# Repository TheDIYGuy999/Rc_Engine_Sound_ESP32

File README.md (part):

# This is an Arduino RC engine sound & light controller for ESP32

It's based on the ATmega 328 version: https://github.com/TheDIYGuy999/Rc_Engine_Sound
and on bitlunis Halloween example: https://github.com/bitluni/MotionPumpkin

Wiring and software installation instructions see further down.
Arduino IDE or Visual Studio Code (with Platform IO extension) are supported.

Video series: https://www.youtube.com/playlist?list=PLGO5EJJClJBCjIvu8frS7LrEU3H2Yz_so

************************************************************************
You can find the changes in the [Changelog](documentation/Changelog.md).
************************************************************************

Discussion and support thread (in German & English): https://www.rc-modellbau-portal.de/index.php?threads/esp32-arduino-rc-sound-und-licht-controller.7183/

Fully assembled, tested and working 30 pin SMD version with switch mode PSU & display connector.
Order it here: https://www.pcbway.com/project/shareproject/Arduino_RC_engine_sound_light_controller_for_ESP32_a9334731.html

New: STL data for nice 3D printed housing available:
https://thediyguy999.github.io/TheDIYGuy999_ESP32_Web_Flasher/products.html

New: Compact version for trailer or tractor:
https://thediyguy999.github.io/TheDIYGuy999_ESP32_Web_Flasher/products.html

New: RZ7886 7A ESC:
https://thediyguy999.github.io/TheDIYGuy999_ESP32_Web_Flasher/products.html

New: wireless built-in configuration website 192.168.4.1

New: LCD dashboard (original by Frevic)

https://www.facebook.com/profile.php?id=100066616574355

LCD dashboard (original by Gamadril)

Fully assembled, tested and working 30 pin SMD version, manufactured and pre-assembled by https://www.pcbway.com

Fully assembled, tested and working 30 pin thru hole version

Compact version for excavator (IBUS & sound only, supplied by 6V BEC)

## Features:
- Unique vehicle mass inertia simulation (connect your crawler type ESC to pin 33). Throttle output is altered during shifting of a mechanical 3 speed transmission for smooth shifting, gear protection and realistic sound. Works just fine with TAMIYA 3 speed transmissions. Should work as well with crawler 2 speed transmissions. The ESC is controlled by a state machine with the following states: driving forward & reverse (varible acceleration, depending on throttle position), neutral, braking forward & reverse (variable deceleration with fine granularity, according to "reverse throttle" position). It also allows to control the brake lights, the brake sound, the reversing light & the reversing beep sound properly. Acceleration & deceleration (coasting & braking) are adjustable separately for each gear to ensure maximum realism.
- Unique "virtual clutch" allows to rev the engine below an adjustable ESC output speed. Above, the clutch engages and ensures, that the engine sound is in synch with the wheel RPM. Sounds and behaves just great in combination with a shifting transmission!
- Simulated automatic transmission with torque converter (if your vehicle does not have a real shifting transmission)
- Simulated double clutch transmission
- simulated, manually shifted 3 speed transmission (new in v5.5)
- Virtual, switchable neutral allows to rev the engine while standing still
- Jake brake (simulated pneumatic engine brake, mainly used in US trucks)
- Tracked mode (dual throttle input on CH2 & CH3, for tanks, diggers etc. No ESC control support in this mode. (New in v4.5)
- Tank cannon sound & flash (New in v4.6)
- Triggering multiple latching and non latching actions (sounds, lights) per analog channel, using the rcTrigger library (New in v4.7, still experimental)
- Many selectable sounds: engine cranking, engine idling, engine revving, turbo whining, diesel ignition "knock", wastegate valve, horns, sirens, reversing beep, air brake, parking brake, gear shifting etc.
- Realistic engine sound is mixed together on the fly from up to 4 sounds: engine idling, turbo, wastegate (all with variable sampling rate), Diesel ignition knock (fixed sampling rate, so it does not vary in pitch)
- Load (throttle position) dependent volume sounds: idle, rev, Diesel knock
- Engine RPM dependent volume sounds: turbo, wastegate
- Dozens of engine & other sounds included, you can also compose your own, using Audacity and bitlunis conversion tool (link above)
- Engine RPM range and inertia adjustable, volume of all sounds adjustable, engine sounds separatly for load and idling.
- Many other paramerets can be adjusted. All adjustments are easily accessible in "adjustmentsXyz.h"
- Sound files up to 22'050Hz, 8bit, mono can be used
- Compatible input signals: PWM, PPM, SBUS (inverted & non inverted signals), IBUS
- Works best with a PAM8403 amplifier module, connected to pin 25 & 26, via 10kOhm resistors & a 10kOhm potentiometer (see schematic below)
- The engine RPM is calculated according to RC signal input on pin 13 *** CAUTION, 3.3V max. on all pins! *** 330 Ohm resistors on all I/O pins recommended!
- Non linear throttle curves can be generated in "curves.h"
- Light effects: headlights (high & low beam), tail lights, brake lights, fog lights, roof lights, cab lights, reversing light, indicators (turn signals), hazard lights, blue light etc. (max. 12 outputs)
- Engine vibration simulation, using a shaker motor with excentric weight: Strong vibration while cranking, medium wlile idling, slight while revving
- Adjustable volume (via remote)
- Use an ESP32, CPU frequency must be set to 240MHz
- Eagle schematic & board file included. Pre made Gerber files allow you to order your board easily.
- included, easy to use .wav to .h sound file converter
- Channels can easily be assigned, using "remoteSetup.h"
- Pre made configuration profiles for Flysky FS-i6X and Arduino Mirco RC remote (new in v.5.5)
- Variable length for horn & siren, using loop area in sound files (new in v5.6)
- BUS decoder for steering servo and shifting servo (connect servos to CH1 & CH2) pins
- Trailer coupler (5th wheel) servo can be connected to the CH4 pins (not in PWM communication mode)
- TAMIYA trailer presence switch can be connected to pin 32 (depending on "#define THIRD_BRAKELIGHT" setting in "6_adjustmentsLights.h" tab)
- Support for non linear throttle and steering curves (for more accurate control around center position). Use "EXPONENTIAL_THROTTLE" & "EXPONENTIAL_STEERING" in "2_adjustmentsRemote.h"
- Support for HOBBYWING Quicrun Fusion Motor / ESC combo. Use "#define QUICRUN_FUSION" in "3_adjustmentsESC.h"
- Support for winch, connected to CH3 (BUS communication mode only). Use "#define MODE2_WINCH" in "7_adjustmentsServo.h" The mode 2 button is then used to switch between horn / siren sontrol and winch control via CH4. The winch is controlled by an old RC servo driver board. The speed and neutral settings are done using "CH3L", CH3C" and CH3R" positions.
- Support for LCD dashboard
- Support for 2812 Neopixel LED (GPIO0)
- Support for hydlaulic excavators (hydraulic pump, hydraulic flow, track rattling sounds). Use #define FLYSKY_FS_I6S_EXCAVATOR profile for remote
- ESP-NOW based 2.4 GHz wireless trailer control support
- An RZ7886 motor driver IC can be used instead of a standard crawler type RC ESC
- Battery low discharge protection options
- Switchable crawler mode (with just minimal virtual inertia)
- Wireless configuration website 192.168.4.1

## On the todo list:
- cornering lights (on the beacon outputs)
- Hazards switching on, if engine off in AUTO_LIGHTS mode

## Known issues:
- Arduino IDE 1.8.7 or older is not supported and will cause compiler errors!
- The ESP32 does not work on macOS Big Sur 11.x, but this issue can be fixed easily as described here: [Big Sur Fix](BigSurFix.md) (for v1.04)
- macOS Monterey 10.3 does not include Python 2 anymore. For Arduino IDE, you have to install Python 3 and to change the path in pPlatform.txt according to:
https://forum.arduino.cc/t/mac-os-update-killed-esp32-sketch/969580/24

## How to create new .h sound files:

### Audacity:
- import the WAV sound file you want in Audacity
- convert it to mono, if needed
- on the bottom left, select project frequency 22'050Hz
- search for a cyclic pattern in the idle sound (the amount of ignition pulses is usually the same as the cylinder number), cut the "idle" sample to exactly this length, have a close look at the zero crossings to avoid clicking noises. The loudest peak should always be at the end of the sample.
- do the same with the "rev" sound. It will be 2 - 4 times shorter than the "idle" sample, depending on the engine and rpm of the "rev" sample
- change the "Rate" (dropdown on the left of the sample) of the "rev" sample, until the length is the same as in the "idle" sample. This is very important!
- duplicate a part of the "rev" sample (the one with the original, unchanged "Rate" speed). This is the "knock" sample. Cut it to this max length: "Idle" length / number of cylinders / rpm range "MAX_RPM_PERCENTAGE" (usually 2 - 4 or 200 - 400%)
- adjust the volume of all samples, so that the entire dynamic range is used
- you may also want to apply high pass or low pass filters to fine tune the sound
- select > export audio > selected audio > WAV > 8-bit-PCM

### Convert the .wav file with the modified converting tool (new in v5.2):

- open the included "Audio2Header.html" converter in your browser. It is located in the "tools" folder
- adjust the export file format (no changes required)
- select the export file type, depending on the sound you are converting (idle, rev, horn etc.)
- open the wav file you want to convert
- a .h file is generated and downloaded
- move it to your "sketch/vehicles/sounds" directory

### Include the new header file with your sound in your vehicle preset, adjust settings until you are happy:
- include this .h file in "Adjustments.h" > "yourVehiclePreset.h"
- knock sound settings:
  - "dieselKnockInterval" = number of cylinders
  - uncomment "V8" for V8 engines, R6 for inline 6 engines or "V2" for V2 (Harley) engines
  - adjust "dieselKnockAdaptiveVolumePercentage" (how loud the "silent" knock pulses are compared with the loud ones), only active, if defined "V8", "R6"  or "V2"
- play with the other volumes, start-, end- and switch-points until you are happy
- the "rev" sound is optional and only active, if "REV_SOUND" is defined (// removed)
- adjust the transition from the "idle" to the "rev" sound, using "revSwitchPoint", "idleEndPoint", "idleVolumeProportionPercentage". This step is very important and can make a huge difference!

### Compile the new sketch:
- compile and upload the sketch in Arduino IDE
- the new sound should now be ready

## Schematic example (use PDF for current version!):

## PCB
### Included PCB files:
- See hardware folder

### Recommended manufacturer:
https://www.pcbway.com (including SMD assembling service, use Gerbers.zip for board, it also includes BOM. xlsx and CPL.xlsx, if you want to use the SMT assembling service)
How to order pre assembled boards see /Eagle_PCB/How To Order Your PCB.pdf

### The easiest way to order the 30pin SMD version with display connector:
https://www.pcbway.com/project/shareproject/Arduino_RC_engine_sound_light_controller_for_ESP32_a9334731.html

### Assembling tutorial (for the 30 pin SMD version without display connector):
https://www.youtube.com/watch?v=csQgTfxRd8Y&t=2s

### Assembling tutorial (for the 36 pin version):
https://www.youtube.com/watch?v=Vfaz3CzecG4&list=PLGO5EJJClJBCjIvu8frS7LrEU3H2Yz_so&index=13

## Wiring:
### Before you begin:
- This device is not protected against wrong polarity!
- Always use series resistors for LED headers (except TAMIYA trailer header)
- Maximum input voltage on "Sig" pins = 3.3V (be careful with very old receivers, which may deliver 5V)
- It is recommended to use a fuse between your battery and the sound controller / ESC

### Supply for audio amplifier, shaker motor and LED:
- Use an Y-cable between your battery, your ESC and The "X1" terminal. Battery voltage range is 7 - 12.6V

### Supply for ESP32:
- The ESP32 is not supplied through the "X1" terminal
- It can be supplied through the Micro USB header
- or through the +V and GND pin row on the top of the board (the voltage is usually coming from the BEC in your ESC, which needs to be connected to the "ESC" header)

### ESC wiring:
- Connect a Hobbywing 1080 ESC to the ESC header (GND, V+ and Sig)
- Adjust the ESC parameters, using the programming card as described on the top of "Adjustments.h"
- I do not recommend any other ESC
- The ESC is controlled by the cound controller, rather than directly by the receiver. This allows to use the unique "virtual inertia" feature. NOTE: Use this feature at your own risk! I'm not responsible, if any damage is caused. It's running very stable and I never had an issue, but you never know.
- "escPulseSpan" can be used to limit the top speed of your vehicle. 500 = not limited, anything above 500 will limit the top speed

### Receiver wiring for PWM servo signals (the most common wiring):
- Channel assignment according to "remoteSetup.h" and remoteSetup.xlsx", easily adjustable (new in v5.5). It is important to plug in the wires according to the channel assignment
- CH5 & 6 are coming in via the "35" & PPM" headers
- At least one CH needs to be connected, using a 3 pin wire, so that GND and V+ are connected as well (receiver supply)
- CH1 - 4 headers are pairs, wired in parallel. This allows to feed servo signals through, eliminating the need for Y-cables
- Note that you need to change the configuration as described below, if you want to use this wiring method

### Receiver wiring for PPM signals:
- Internal channel assignment as above
- Connect a 3 pin wire fom your receiver PPM header to the RX (changed in v5.5, was PPM) header on the sound controller (Sig, V+, GND)
- Note that you need to change the configuration as described below, if you want to use this wiring method
- 8 channels can be read in this mode

### Receiver wiring for SBUS signals (recommended):
- Internal channel assignment as above
- Connect a 3 pin wire fom your receiver SBUS header to the SBUS header on the sound controller (Sig, V+, GND)
- The "Sig" pin on the SBUS header is 5V tolerant
- 13 channels can be read in this mode

### Receiver wiring for IBUS signals:
- Internal channel assignment as above
- Connect a 3 pin wire fom your receiver IBUS header to the RX header on the sound controller (Sig, V+, GND)
- 13 channels can be read in this mode

### Speakers
- 4 or 8 ohms speakers are compatible
- You can use one or two speakers
- never use two speakers in parallel on a single header
- never use two headers in parallel to drive one speaker
- never connect capacitors to the speaker headers

### LED
- The LED need to be wired "common positive". This means, the long LED legs are all connected together and connect to the 5V rail, coming from the on board regulator
- All LED (except the ones, which are connected to the TAMIYA trailer connector) need a series resistor
- Calculate the reqired resistor according to: http://ledcalc.com (supply voltage = 5V)
- It is not recommended to wire LED in parallel, sharing the series resistor
- Support for WS2812 Neopixel LED (details and wiring see "6_adjustmentsLights.h")

### LCD dashboard
- See "9_adjustmentsDashboard.h"

### Shaker
- The shaker is used for engine vibration simulation. The speed can be adjusted in the vehicle configuration and will vary depending on the engine state and rpm
- It needs to be connected to the "shaker" header and is supplied by the on board 5V regulator. The negative side is switched by the on board mosfet
- Please note, that the used mosfet needs to be a logic level type. Otherwise the shaker will not work!
- The motor should not draw more than about 300mA @ 5V. I'm using a shaker motor from GT Power.

### RZ7886 7A DC motor driver instead of an ESC:
It is intended for smaller scale vehicles like WPL

#### Prototype:

#### Order your motor driver PCB here:
https://www.pcbway.com/project/shareproject/RZ7886_based_ESC_for_ESP32_Sound_and_Light_Controller_f8f4a805.html

## Software:
### Required software for code uploading and editing:
- Arduino IDE (not recommnded): https://www.arduino.cc/en/Main/Software
- or Visual Studio Code with PlatformIO extension (recommended): https://code.visualstudio.com
- Visual Studio also requires this software (restart VS Code afterwards) in order to be able to synchronise libraries: https://git-scm.com/download

### Downloading and preparing the code with Arduino IDE:
- Download the code from here (hit "Code > Download zip"): https://github.com/TheDIYGuy999/Rc_Engine_Sound_ESP32
- Unzip the folder, if required
- Remove the "-master" part of the folder name
- Install libraries and board definitions below first, restart Arduino IDE
- Open "scr.ino" with a double click (Arduino IDE should start)

### Required ESP32 board definition (not required, if Visual Studio Code is used as IDE):
- Install it according to: https://randomnerdtutorials.com/installing-the-esp32-board-in-arduino-ide-windows-instructions/
- Use v1.04, v1.05 or newer are causing reboot issues!
- Adjust settings according to:

### Required libraries. You need to install ALL of them, if using Arduino IDE. Not required, if Visual Studio Code is used as IDE:
- statusLED: https://github.com/TheDIYGuy999/statusLED
- SBUS: https://github.com/TheDIYGuy999/SBUS
- rcTrigger: https://github.com/TheDIYGuy999/rcTrigger
- IBUS: https://github.com/bmellink/IBusBM
- TFT: https://github.com/Bodmer/TFT_eSPI
- FastLED: https://github.com/FastLED/FastLED    

Download them in the same manner as the main code above. Store the folders in your "Arduino/libraries" path.
Install them according to: https://www.arduino.cc/en/Guide/Libraries

### Uploading the code to the board:
- IMPORTANT: Depending on your board, you may have to press and hold the "BOOT" button, if the IDE just shows "Connecting........_____...." Release it, as soon as the upload starts.
- On macOS Big Sur, you need to apply the following fix (Arduino IDE only):  [Big Sur Fix](BigSurFix.md)

### Visual Studio Code (instead of Arduino IDE) overiew:

## Adjusting things in "X_Xyz.h":
### Vehicle selection:

Note, that in v5.5 the former "Adjustments.h" configuration file was divided into multiple files.

Uncomment (remove //) the vehicle you want in "Adjustments.h". Never uncomment more than one vehicle!
Note, that you need to re-upload the code after you changed the settings. Otherwise it will not take effect.
Select >Sketch > Upload to upload the code. Important! Always lift your vehicle off the ground while uploading.

If you want to make a new vehicle, copy vehicles/00_Master.h, store it with your vehicle name. Then edit the settings as you like, add links to the sound files you want.
Afterwards add a link to your vehicle.h (see examples below) and uncomment it

```
#include <Arduino.h>

// VEHICLE SETTINGS ****************************************************************************************************
// Select the vehicle preset you want (uncomment the one you want, remove //, never more than one)

// Master --------
//#include "vehicles/00_Master.h" // This master preset file contains all available sound files, which are not used in existing vehicle presets

// US trucks --------
//#include "vehicles/CaboverCAT3408.h" // Cabover truck with Caterpillar 3408 V8 Diesel
//#include "vehicles/PeterbiltDetroit8v92.h" // Peterbilt 359 with Detroit 8V92 V8 2 stroke Diesel
//#include "vehicles/KenworthW900ADetroit8V71.h" // Kenworth W900A with Detroit 8V71 V8 2 stroke Diesel
//#include "vehicles/KenworthW900ACAT3408.h" // Kenworth W900A with Caterpillar 3408 V8 Diesel (King Hauler)
//#include "vehicles/CAT3408OpenPipes.h" // Kenworth W900A with Caterpillar 3408 V8 Diesel and open pipes
//#include "vehicles/KenworthW900ACAT3408new.h" // Kenworth W900A with Caterpillar 3408 V8 Diesel (good bass speaker required)
//#include "vehicles/KenworthCummins335.h" // 1950ies Kenworth with Cummins 335 R6 Diesel
//#include "vehicles/MackSuperLiner.h" // MACK Super Liner
//#include "vehicles/M35.h"// AM General M35 "deuce and a half" military truck, turbocharged R6 universal fuel engine
//#include "vehicles/US_Firetruck.h"// US firetruck with CAT3408 V8 and Allison 6 speed automatic (horn & siren loop capable)
//#include "vehicles/FreightlinerCummins350.h" // Freightliner Cabover with Cummins 350 R6 Diesel

// EU trucks --------
//#include "vehicles/Tatra813.h" // Tatra 813 8x8 V12 Diesel military truck (old version for comparison, don't use it)
//#include "vehicles/Tatra813new.h" // Tatra 813 8x8 V12 Diesel military truck
//#include "vehicles/UnimogU1000.h" // Umimog U 1000 with turbocharged R6 Diesel incl. Feuerwehr "Martinshorn" siren
//#include "vehicles/MercedesActros1836.h" // Mercedes Actros 1863 or 3363 truck with R6 Diesel
//#include "vehicles/MercedesActrosV6.h" // Mercedes Actros V6 Race Truck incl. tire squealing
//#include "vehicles/ScaniaV8_50ton.h" // SCANIA V8 50 ton truck. Unknown model. Bad quality!
//#include "vehicles/ScaniaV8.h" // SCANIA V8 truck, unknown model
//#include "vehicles/1000HpScaniaV8.h" // 1000 HP SCANIA V8 truck with open pipes. Insane sound! Good bass speakers reqired
//#include "vehicles/Scania143.h" // SCANIA 143 V8 - the legend! The best sounding in my opinion
//#include "vehicles/ScaniaV8Firetruck.h" // SCANIA V8 firetruck, automatic Allison 6 speed transmission with torque converter, "Martinshorn" siren
//#include "vehicles/VolvoFH16_750.h" // Volvo FH16 750 truck. Inline 6, 750 horses, open pipes!
//#include "vehicles/VolvoFH16_OpenPipe.h" // Volvo FH truck. Inline 6, open pipes, alternative version
//#include "vehicles/ManTgx.h" // MAN TGX 680 V8 truck
//#include "vehicles/ManKat.h" // MAN KAT V8 Diesel German Bundeswehr military truck
//#include "vehicles/MagirusDeutz256.h" // Magirus Deutz 256 air coolded V8 Diesel truck
//#include "vehicles/MagirusMercur125.h" // Magirus Mercur air coolded V6 Diesel truck
//#include "vehicles/Saurer2DM.h" // Swiss Saurer 2DM R6 Diesel truck

// Russian trucks --------
//#include "vehicles/Ural4320.h" // URAL 4320 6x6 V8 Diesel military truck
#include "vehicles/Ural375D.h" // URAL 375D 6x6 V8 petrol military truck
//#include "vehicles/URAL375.h" // URAL 375D 6x6 V8 petrol military truck (new version with better V8 sound, but good bass speaker required)
//#include "vehicles/GAZ66.h" // GAZ-66 V8 petrol military truck

// Russian tanks -------
//#include "vehicles/IS3.h" // IS-3 WW2 battle tank, V12 Diesel (dual ESC mode, good bass speaker required)

// Tractors -------
//#include "vehicles/KirovetsK700.h" // Russian Kirovets K700 monster tractor. Extreme turbo sound!

// Excavators -------
//#include "vehicles/Caterpillar323Excavator.h" // Caterpillar 323 excavator (use "FLYSKY_FS_I6S_EXCAVATOR" remote profile)

// Dumpers -------
//#include "vehicles/Benford3TonDumper.h" // Benford 3 ton dumper

// US motorcycles --------
//#include "vehicles/HarleyDavidsonFXSB.h" // Harley Davidson FXSB V2 motorcycle

// US cars --------
//#include "vehicles/ChevyNovaCoupeV8.h" // 1975 Chevy Nova Coupe V8
//#include "vehicles/1965FordMustangV8.h"// 1965 Ford Mustang V8
//#include "vehicles/Chevy468.h" // Chevy 468 big block V8

// EU cars --------
//#include "vehicles/VwBeetle.h" // VW Käfer / Beetle
//#include "vehicles/JaguarXJS.h" // Jaguar XJS V12, manual transmission
//#include "vehicles/JaguarXJSautomatic.h" // Jaguar XJS V12, automatic transmission
//#include "vehicles/MGBGtV8.h" // MGB GT V8, manual transmission
//#include "vehicles/LaFerrari.h" // Ferrari LaFerrari, V12, 6 speed double clutch transmission

// US SUV & Pickups --------
//#include "vehicles/JeepGrandCherokeeTrackhawk.h" // Jeep Grand Cherokee Trackhawk V8 monster SUV with supercharger, 6 speed automatic
//#include "vehicles/FordPowerstroke.h" // Ford Powerstroke 7.3l V8 Diesel, 6 speed automatic (good bass speaker required)
//#include "vehicles/RAM2500_Cummins12V.h" // Dodge RAM 2500 with inline 6, 12V Cummins 5.9l Diesel, manual transmission
//#include "vehicles/RAM2500_Cummins12Vautomatic.h" // Dodge RAM 2500 with inline 6, 12V Cummins 5.9l Diesel, automatic transmission
//#include "vehicles/GMCsierra.h" // GMC Sierra V8 pickup, 3 speed automatic transmission
//#include "vehicles/ChevyNovaCoupeV8_P407.h" // 1975 Chevy Nova Coupe V8, special version for HG-P407, 3 speed automatic transmission
//#include "vehicles/JeepWranglerRubicon392V8.h" // 2021 Jeep Wrangler Rubicon HEMI 392 V8 (starter needs rework)
//#include "vehicles/JeepWranglerRubicon392V8_2.h" // 2021 Jeep Wrangler Rubicon HEMI 392 V8 (insane bass!)

// EU SUV --------
//#include "vehicles/DefenderV8Automatic.h" // Land Rover Defender 90 V8 automatic (very nice V8 with lots of bass)
//#include "vehicles/DefenderV8OpenPipeAutomatic.h" // Land Rover Defender 90 V8 automatic, open pipes (optimised for smaller speakers)
//#include "vehicles/DefenderV8CrawlerAutomatic.h" // Land Rover Defender 90 V8 automatic crawler
//#include "vehicles/DefenderTd5.h" // Land Rover Defender 90 Td5 R5 Diesel

// Asian SUV --------
//#include "vehicles/LandcruiserFJ40.h" // Landcruiser Fj40 with inline 6 petrol engine
//#include "vehicles/LandcruiserFJ40Diesel.h" // Landcruiser Fj40 with inline 6 12H Turbo Diesel engine
//#include "vehicles/LandcruiserFJ40Diesel2.h" // Landcruiser Fj40 with inline 6 12H Turbo Diesel engine
//#include "vehicles/HiluxDiesel.h" // Hilux Diesel with inline 6 12H Turbo Diesel engine (for HG-P407)

// US locomotives --------
//#include "vehicles/UnionPacific2002.h" // Union Pacific 2002 SD70M locomotive with enormous, low revving 16 cylinder Diesel

// Planes --------
//#include "vehicles/MesserschmittBf109.h" // Messerschmitt BF 109 WW2 German V12 plane

// Generic Diesels --------
//#include "vehicles/generic6zylDiesel.h" // Generic inline 6 Diesel, no turbo, manual transmission (optimised for smaller speakers)
```

### Interface type (communication mode) selection:

Note, that the default communication mode is SBUS. You need to change it as follows, if you want to use classic RC servo signals.

#### PWM (classic RC signals on "CH1" - "CH4", "35" & "PPM" headers, the most common interface)
```
// COMMUNICATION SETTINGS **********************************************************************************************
// Choose the receiver communication mode (never uncomment more than one!) !!! ADJUST THEM BEFORE CONNECTING YOUR RECEIVER AND ESC !!!

// PWM servo signal communication (CH1 - CH4, 35, PPM headers, 6 channelschannelSetup.h) --------
// PWM mode active, if SBUS, IBUS and PPM are disabled (// in front of #define)

// SBUS communication (SBUS header, 13 channels. This my preferred communication protocol)--------
//#define SBUS_COMMUNICATION // control signals are coming in via the SBUS interface (comment it out for classic PWM RC signals)
boolean sbusInverted = true; // false = wired to non standard (inverted) SBUS signal (for example from "Micro RC" receiver)

// IBUS communication (RX header, 13 channels not recommended, NO FAILSAFE, if bad contact in iBUS wiring!) --------
//#define IBUS_COMMUNICATION // control signals are coming in via the IBUS interface (comment it out for classic PWM RC signals)

// SUMD communication (RX header, 12 channels, For Graupner remotes) --------
//#define SUMD_COMMUNICATION // control signals are coming in via the SUMD interface (comment it out for classic PWM RC signals)

// PPM communication (RX header, 8 channels, working fine, but channel signals are a bit jittery) --------
//#define PPM_COMMUNICATION // control signals are coming in via the PPM interface (comment it out for classic PWM RC signals)
```

#### PPM (multiple channels pulse pause modulation, wired to "RX" header, 8 channels)
```
// COMMUNICATION SETTINGS **********************************************************************************************
// Choose the receiver communication mode (never uncomment more than one!) !!! ADJUST THEM BEFORE CONNECTING YOUR RECEIVER AND ESC !!!

// PWM servo signal communication (CH1 - CH4, 35, PPM headers, 6 channelschannelSetup.h) --------
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
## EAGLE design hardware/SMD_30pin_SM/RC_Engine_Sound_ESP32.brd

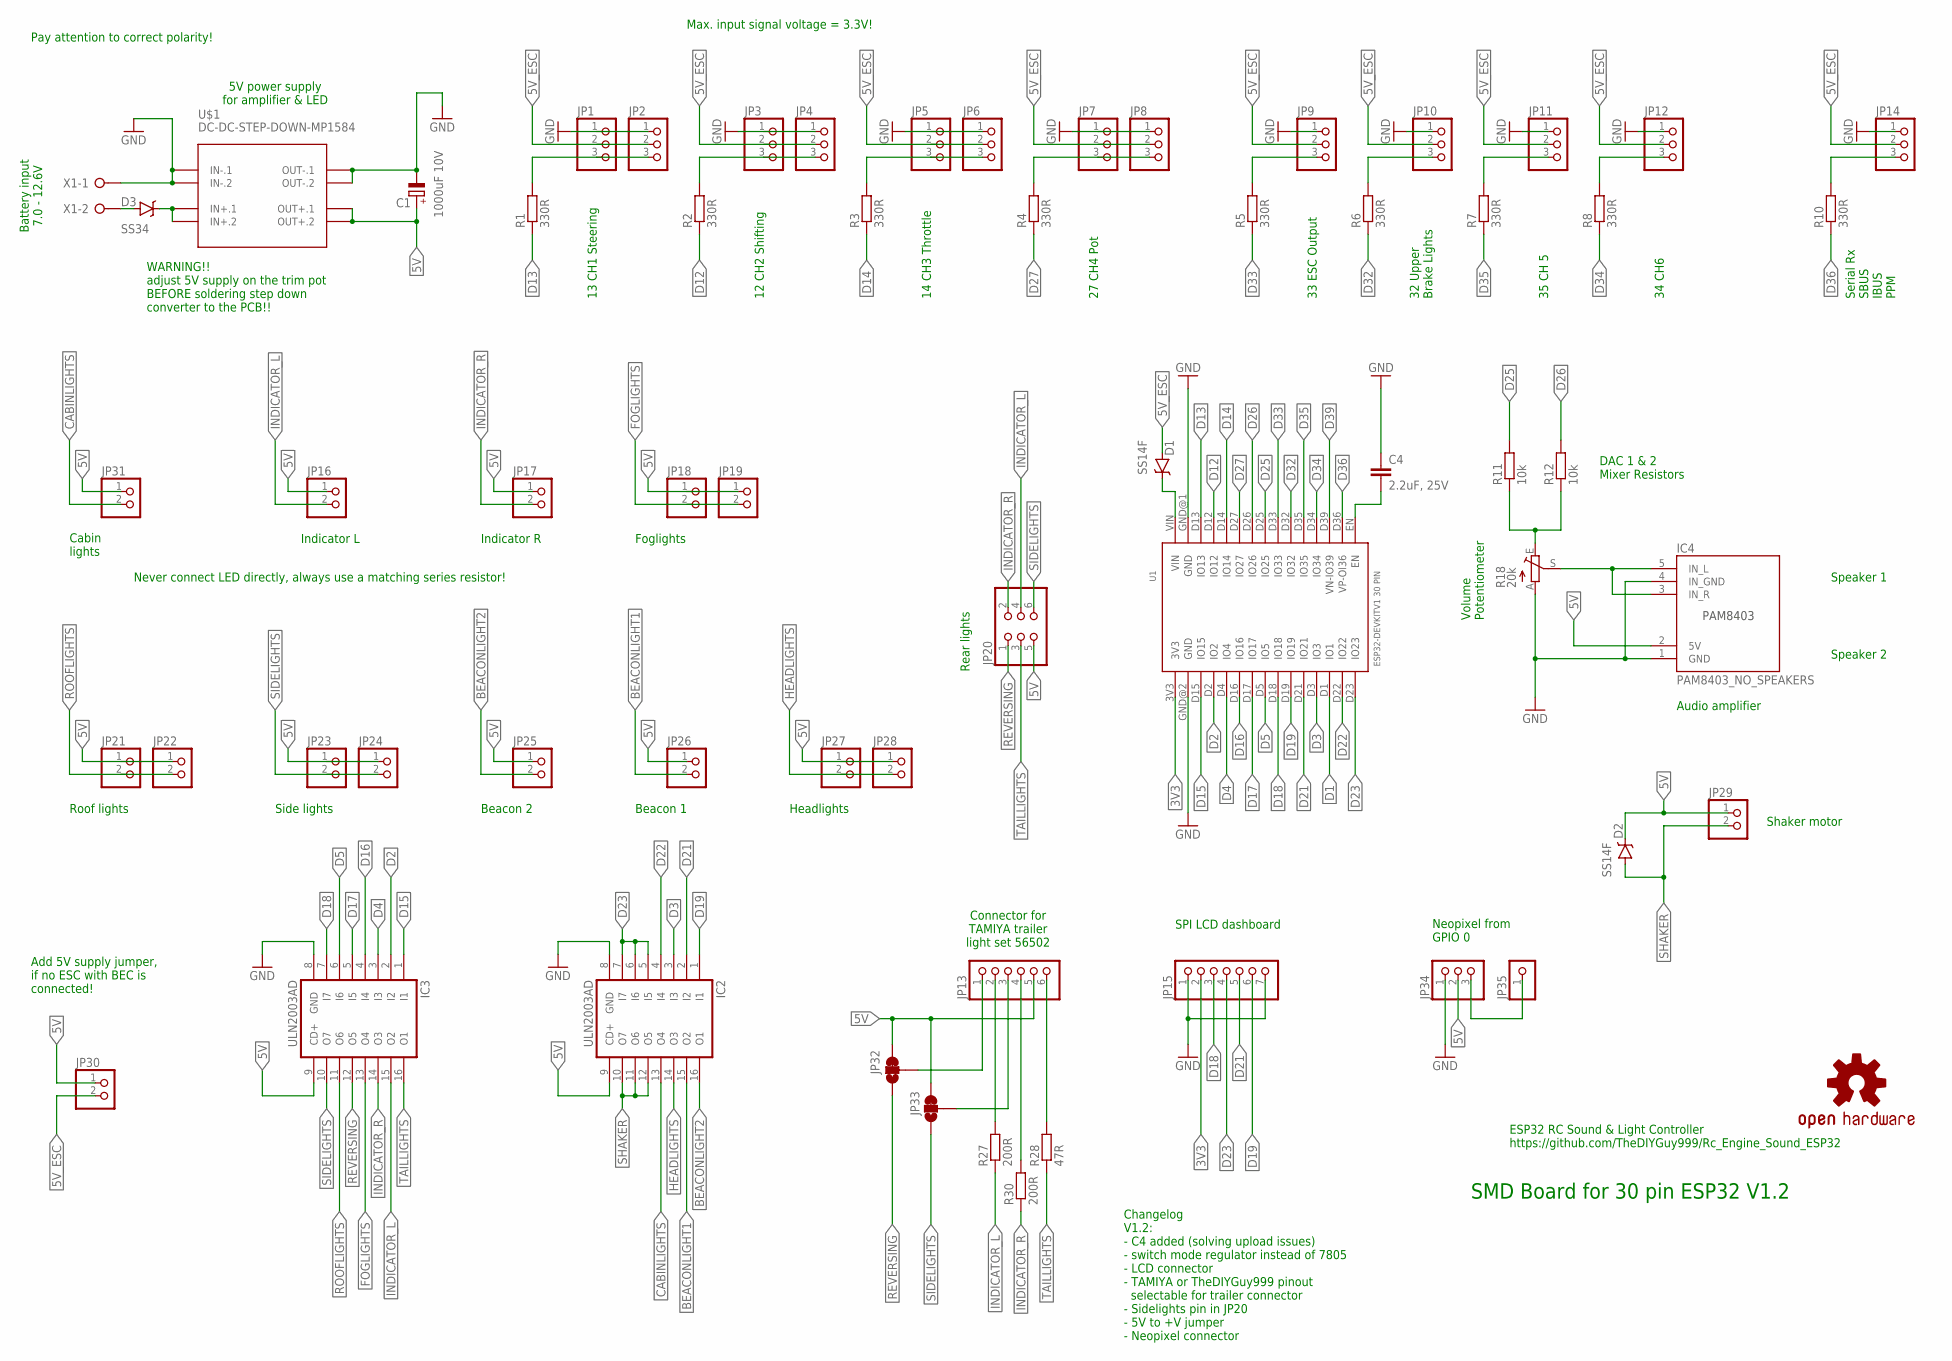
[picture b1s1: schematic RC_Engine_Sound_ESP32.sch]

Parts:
C1: 1000uF 10V; UD-10X10_NICHICON
C4: 2.2uF, 25V; C1206
D1, D2: SS14F; SMA-DIODE
D3: SS34; SMA-DIODE
IC2, IC3: ULN2003AD; SO16
IC4: PAM8403_NO_SPEAKERS
JP1, JP2, JP3, JP4, JP5, JP6, JP7, JP8, JP9, JP10, JP11, JP12, JP14, JP34: PINHD-1X3; 1X03
JP13: PINHD-1X6; 1X06
JP15: PINHD-1X7; 1X07
JP16, JP17, JP18, JP19, JP21, JP22, JP23, JP24, JP25, JP26, JP27, JP28, JP29, JP30, JP31: PINHD-1X2; 1X02
JP20: PINHD-2X3; 2X03
JP32, JP33: JUMPER-PAD-3-2OF3_NC_BY_TRACE_LARGE; PAD-JUMPER-3-2OF3_NC_BY_TRACE_YES_SILK_LARGE
JP35: PINHD-1X1; 1X01
LOGO1: OSHW-LOGOM; OSHW-LOGO-M
R1, R2, R3, R4, R5, R6, R7, R8, R10: 330R; R0805
R11, R12: 10k; R0805
R18: 20k; S64W
R27, R30: 200R; R0805
R28: 47R; R0805
U1: ESP32DEVKITV1; ESP32-DEVKITV1
U$1: DC-DC-STEP-DOWN-MP1584
X1: W237-02P; W237-132

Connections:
3V3: JP15.2, U1.3V3
5V: C1.+, D2.C, IC2.9 (CD+), IC3.9 (CD+), IC4.2 (5V), JP13.5, JP16.1, JP17.1, JP18.1, JP19.1, JP20.5, JP21.1, JP22.1, JP23.1, JP24.1, JP25.1, JP26.1, JP27.1, JP28.1, JP29.1, JP30.1, JP31.1, JP32.3, JP33.3, JP34.2, U$1.OUT+.1, U$1.OUT+.2
5V_ESC: D1.A, JP1.2, JP2.2, JP3.2, JP4.2, JP5.2, JP6.2, JP7.2, JP8.2, JP9.2, JP10.2, JP11.2, JP12.2, JP14.2, JP30.2
BEACONLIGHT1: IC2.15 (O2), JP26.2
BEACONLIGHT2: IC2.16 (O1), JP25.2
CABINLIGHTS: IC2.13 (O4), JP31.2
D0: JP34.3, JP35.1
D1: U1.D1 (IO1)
D2: IC3.2 (I2), U1.D2 (IO2)
D3: IC2.3 (I3), U1.D3 (IO3)
D4: IC3.3 (I3), U1.D4 (IO4)
D5: IC3.6 (I6), U1.D5 (IO5)
D12: R2.1, U1.D12 (IO12)
D13: R1.1, U1.D13 (IO13)
D14: R3.1, U1.D14 (IO14)
D15: IC3.1 (I1), U1.D15 (IO15)
D16: IC3.4 (I4), U1.D16 (IO16)
D17: IC3.5 (I5), U1.D17 (IO17)
D18: IC3.7 (I7), JP15.3, U1.D18 (IO18)
D19: IC2.1 (I1), JP15.6, U1.D19 (IO19)
D21: IC2.2 (I2), JP15.5, U1.D21 (IO21)
D22: IC2.4 (I4), U1.D22 (IO22)
D23: IC2.5 (I5), IC2.6 (I6), IC2.7 (I7), JP15.4, U1.D23 (IO23)
D25: R11.2, U1.D25 (IO25)
D26: R12.2, U1.D26 (IO26)
D27: R4.1, U1.D27 (IO27)
D32: R6.1, U1.D32 (IO32)
D33: R5.1, U1.D33 (IO33)
D34: R8.1, U1.D34 (IO34)
D35: R7.1, U1.D35 (IO35)
D36: R10.1, U1.D36 (VP-OI36)
D39: U1.D39 (VN-IO39)
FOGLIGHTS: IC3.13 (O4), JP18.2, JP19.2
GND: C1.-, C4.1, IC2.8 (GND), IC3.8 (GND), IC4.1 (GND), IC4.4 (IN_GND), JP1.1, JP2.1, JP3.1, JP4.1, JP5.1, JP6.1, JP7.1, JP8.1, JP9.1, JP10.1, JP11.1, JP12.1, JP14.1, JP15.1, JP15.7, JP34.1, R18.A, U1.GND@1 (GND), U1.GND@2 (GND), U$1.IN-.1, U$1.IN-.2, U$1.OUT-.1, U$1.OUT-.2, X1.1
HEADLIGHTS: IC2.14 (O3), JP27.2, JP28.2
INDICATOR_L: IC3.15 (O2), JP16.2, JP20.4, R27.1
INDICATOR_R: IC3.14 (O3), JP17.2, JP20.2, R30.1
unnamed: IC4.3 (IN_R), IC4.5 (IN_L), R18.S
unnamed: R11.1, R12.1, R18.E
unnamed: JP1.3, JP2.3, R1.2
unnamed: JP13.6, R28.2
unnamed: JP3.3, JP4.3, R2.2
unnamed: JP5.3, JP6.3, R3.2
unnamed: JP7.3, JP8.3, R4.2
unnamed: JP9.3, R5.2
unnamed: D1.C, U1.VIN
unnamed: JP10.3, R6.2
unnamed: JP11.3, R7.2
unnamed: JP12.3, R8.2
unnamed: JP13.4, R30.2
unnamed: JP14.3, R10.2
unnamed: JP13.2, R27.2
unnamed: JP13.1, JP32.2
unnamed: C4.2, U1.EN
unnamed: JP13.3, JP33.2
unnamed: D3.C, U$1.IN+.1, U$1.IN+.2
unnamed: D3.A, X1.2
REVERSING: IC3.12 (O5), JP20.1, JP32.1
ROOFLIGHTS: IC3.11 (O6), JP21.2, JP22.2
SHAKER: D2.A, IC2.10 (O7), IC2.11 (O6), IC2.12 (O5), JP29.2
SIDELIGHTS: IC3.10 (O7), JP20.6, JP23.2, JP24.2, JP33.1
TAILLIGHTS: IC3.16 (O1), JP20.3, R28.1

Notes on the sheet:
Speaker 1
Speaker 2
13 CH1 Steering
12 CH2 Shifting
14 CH3 Throttle
27 CH4 Pot
33 ESC Output
32 Upper Brake Lights
35 CH 5
34 CH6
Serial Rx SBUS IBUS PPM
DAC 1 & 2 Mixer Resistors
Audio amplifier
Volume Potentiometer
5V power supply for amplifier & LED
Battery input 7.0 - 12.6V
SMD Board for 30 pin ESP32 V1.2
Shaker motor
Headlights
Foglights
Indicator L
Indicator R
Roof lights
Side lights
Connector for TAMIYA trailer light set 56502
Rear lights
ESP32 RC Sound & Light Controller https://github.com/TheDIYGuy999/Rc_Engine_Sound_ESP32
Never connect LED directly, always use a matching series resistor!
Beacon 2
Beacon 1
Cabin lights
Pay attention to correct polarity!
Max. input signal voltage = 3.3V!
Changelog V1.2: - C4 added (solving upload issues) - switch mode regulator instead of 7805 - LCD connector - TAMIYA or TheDIYGuy999 pinout selectable for trailer connector - Sidelights pin in JP20 - 5V to +V jumper - Neopixel connector
WARNING!! adjust 5V supply on the trim pot BEFORE soldering step down converter to the PCB!!
SPI LCD dashboard
Add 5V supply jumper, if no ESC with BEC is connected!
Neopixel from GPIO 0

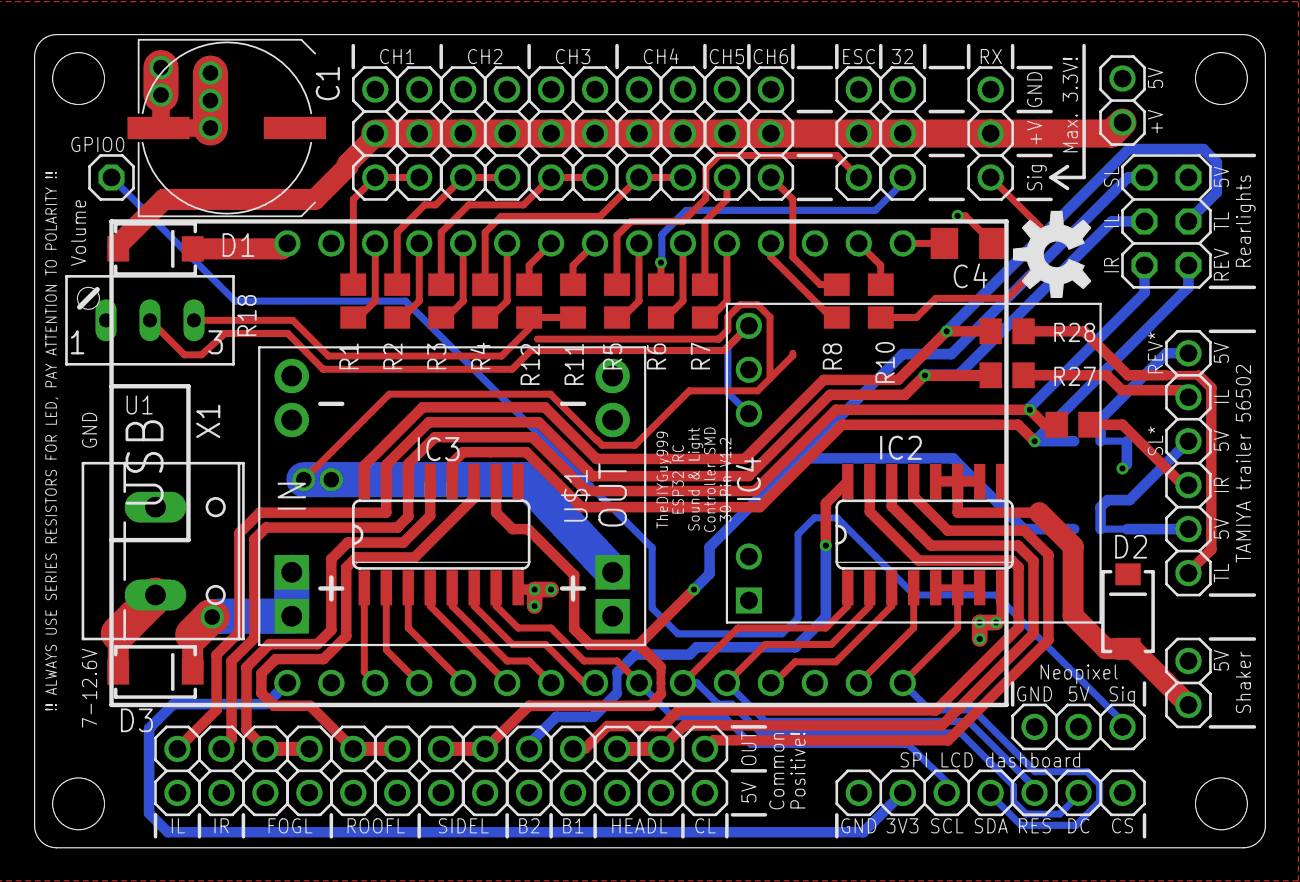
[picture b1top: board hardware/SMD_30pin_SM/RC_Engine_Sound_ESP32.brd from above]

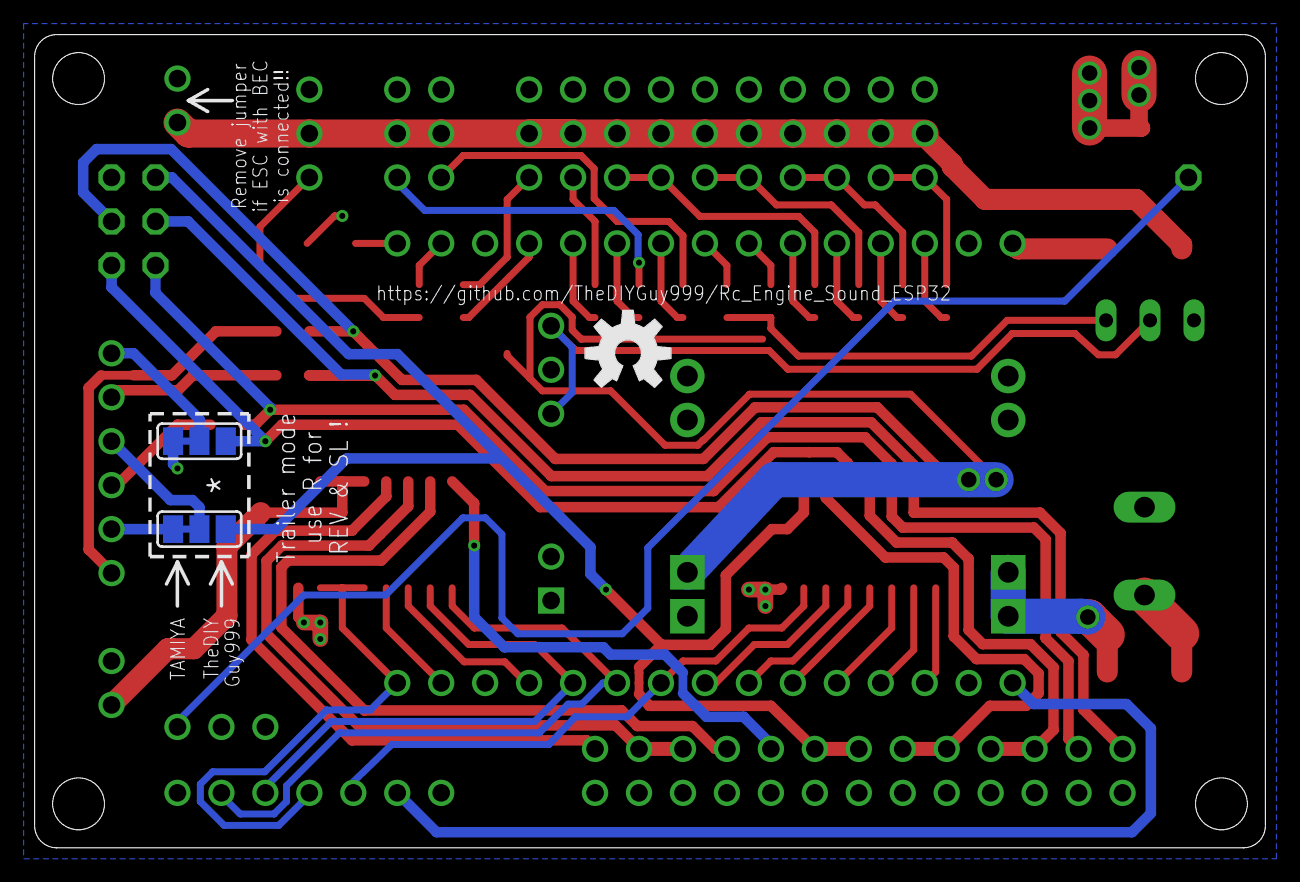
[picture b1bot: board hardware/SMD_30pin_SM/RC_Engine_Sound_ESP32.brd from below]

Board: 2 copper layers, 71.1 x 47.0 mm, 63 parts (3 on the bottom side), 60 nets.

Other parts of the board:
LOGO2: OSHW-LOGOM; OSHW-LOGO-M

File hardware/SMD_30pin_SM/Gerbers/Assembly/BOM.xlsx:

Comment | Designator | QTY | Footprint | LCSC Part #（optional） | Additional Comment
 | JP35 | 1 | 1X01
 | JP16, JP17, JP18, JP19, JP21, JP22, JP23, JP24, JP25, JP26, JP27, JP28, JP29, J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 | 15 | 1X02
 | JP1, JP2, JP3, JP4, JP5, JP6, JP7, JP8, JP9, JP10, JP11, JP12, JP14,JP34 | 14 | 1X03
 | JP13 | 1 | 1X06
 | JP15 | 1 | 1X07
 | JP20 | 1 | 2X03
WAGO SREW CLAMP | X1 | 1 | W237-132
1000uF 10V | C1 | 1 | SMD-ECAP-10x10
2.2uF 25V | C4 | 1 | C1206
10k | R11, R12 | 2 | R0805
200R | R27, R30 | 2 | R0805
20k | R18 | 1 | S64W |  | Potentiometer
330R | R1, R2, R3, R4, R5, R6, R7, R8, R10 | 9 | R0805
47R | R28 | 1 | R0805
DC-DC-STEP-DOWN-MP1584 | U$1 | 1 | custom
ESP32DEVKITV1 | U1 | 1 | ESP32-DEVKITV1
JUMPER-PAD-3-2OF3_NC_BY_TRACE_LARGE | JP32, JP33 | 2
OSHW-LOGOM | LOGO1 | 1 | OSHW-LOGO-M
PAM8403_NO_SPEAKERS | IC4 | 1 | PAM8403_NO_SPEAKERS
SS14 | D1, D2 | 2 | SMA-DIODE DO-214AC |  | 40V, 1A Schottky rectifier
SS34 | D3 | 1 | SMA-DIODE DO-214AC |  | 40V, 3A Schottky rectifier
ULN2003AD | IC2, IC3 | 2 | SO16
 | Parts suppliers and tolerances are not important. Please ask back, if any of th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
 | Do not populate

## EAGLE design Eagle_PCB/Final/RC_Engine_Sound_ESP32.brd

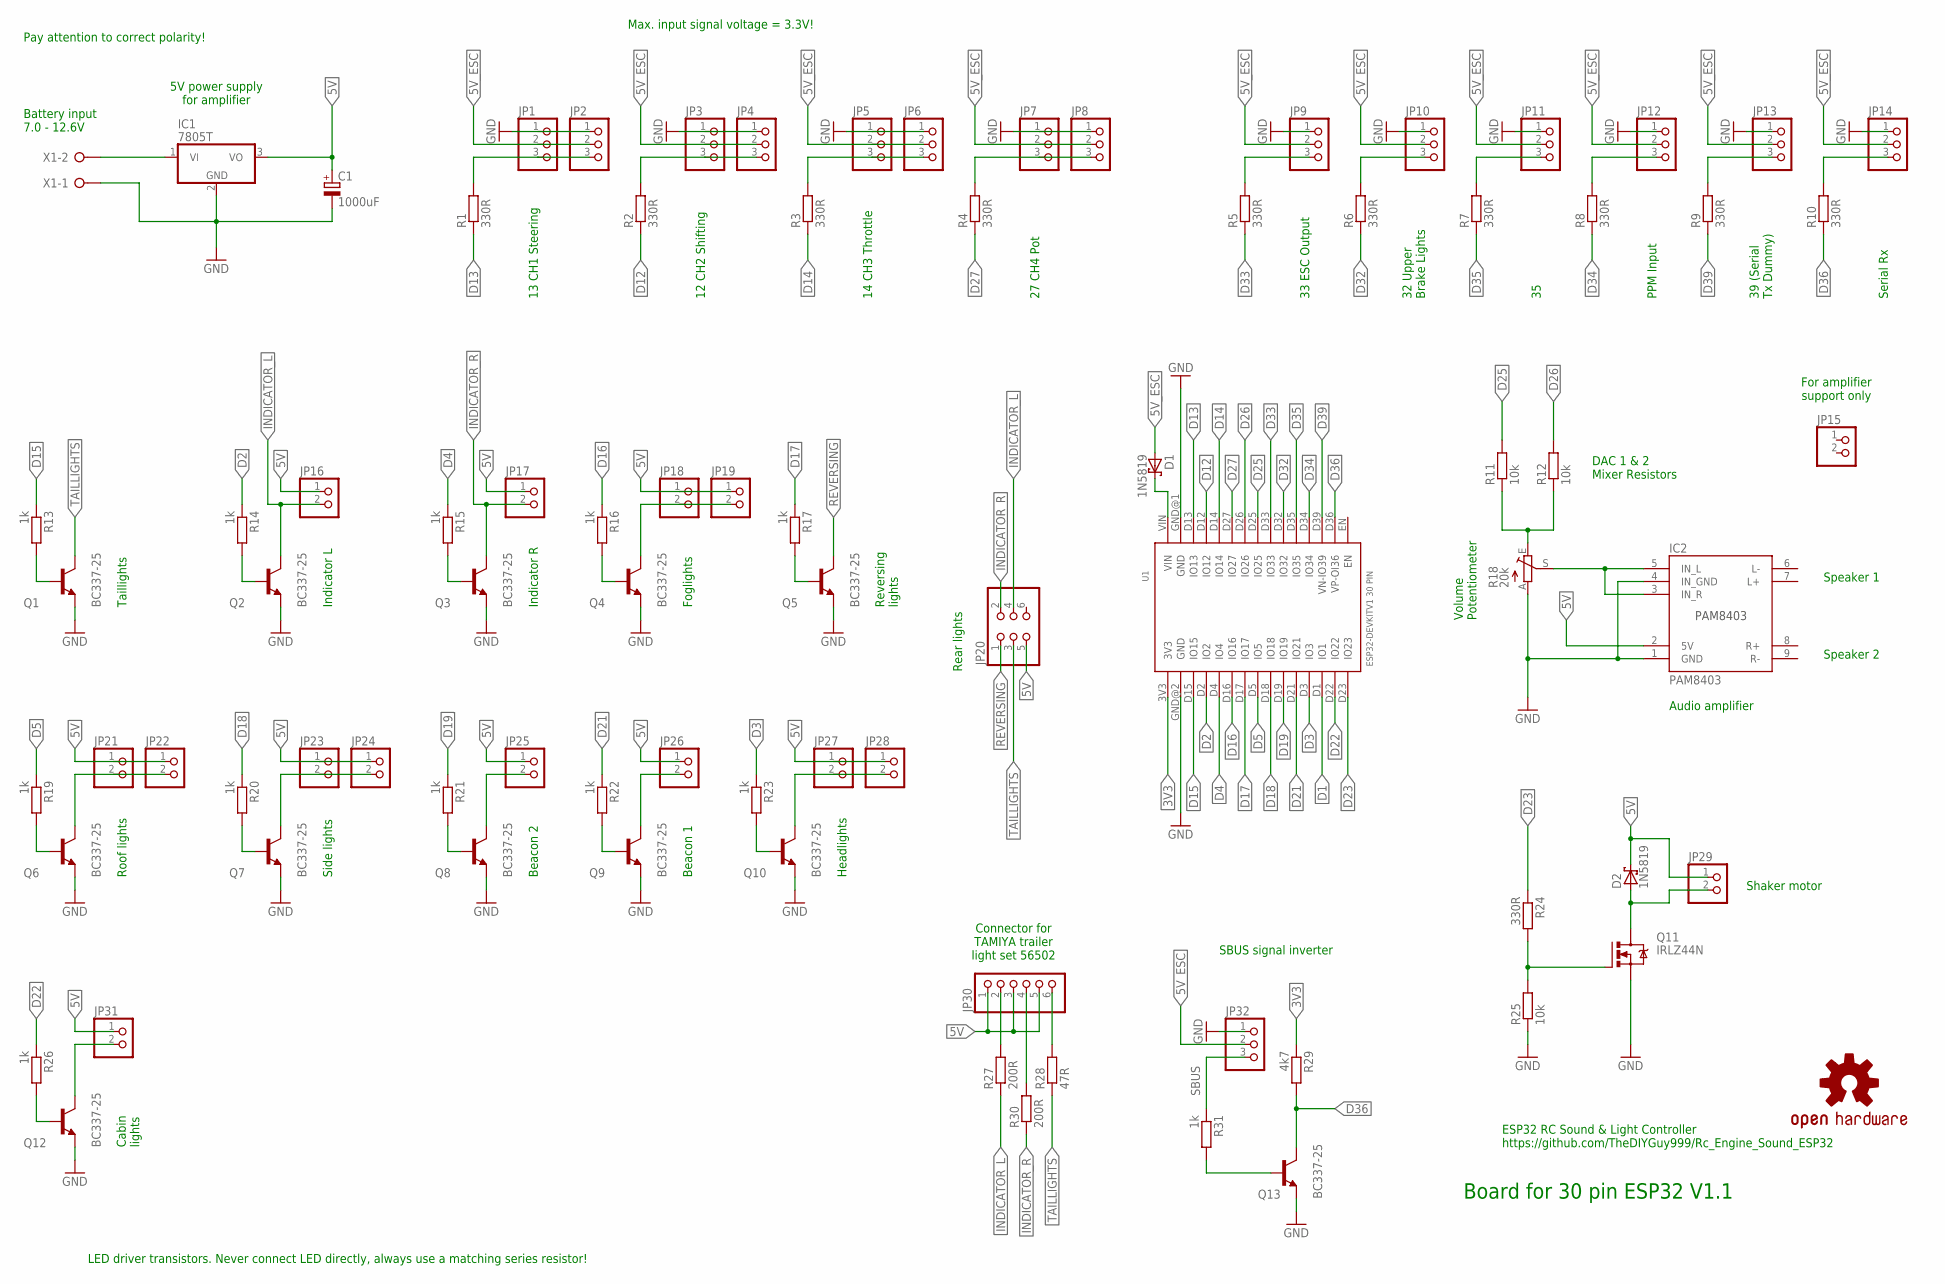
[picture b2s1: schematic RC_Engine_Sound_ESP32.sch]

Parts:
C1: 1000uF; E5-10,5
D1, D2: 1N5819; DO35-7
IC1: 7805T; TO220H
IC2: PAM8403
JP1, JP2, JP3, JP4, JP5, JP6, JP7, JP8, JP9, JP10, JP11, JP12, JP13, JP14, JP32: PINHD-1X3; 1X03
JP15, JP16, JP17, JP18, JP19, JP21, JP22, JP23, JP24, JP25, JP26, JP27, JP28, JP29, JP31: PINHD-1X2; 1X02
JP20: PINHD-2X3; 2X03
JP30: PINHD-1X6; 1X06
LOGO1: OSHW-LOGOM; OSHW-LOGO-M
Q1, Q2, Q3, Q4, Q5, Q6, Q7, Q8, Q9, Q10, Q12, Q13: BC337-25; TO92
Q11: IRLZ44N; TO220BV
R1, R2, R3, R4, R5, R6, R7, R8, R9, R10, R24: 330R; 0207/2V
R11, R12: 10k; 0207/10
R13, R14, R15, R16, R17, R19, R20, R21, R22, R23, R26, R31: 1k; 0207/2V
R18: 20k; S64W
R25: 10k; 0207/2V
R27, R30: 200R; 0207/10
R28: 47R; 0207/10
R29: 4k7; 0207/2V
U1: ESP32DEVKITV1; ESP32-DEVKITV1
X1: W237-02P; W237-132

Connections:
3V3: R29.1, U1.3V3
5V: C1.+, D2.C, IC1.3 (VO), IC2.2 (5V), JP16.1, JP17.1, JP18.1, JP19.1, JP20.5, JP21.1, JP22.1, JP23.1, JP24.1, JP25.1, JP26.1, JP27.1, JP28.1, JP29.1, JP30.1, JP30.3, JP30.5, JP31.1
5V_ESC: D1.A, JP1.2, JP2.2, JP3.2, JP4.2, JP5.2, JP6.2, JP7.2, JP8.2, JP9.2, JP10.2, JP11.2, JP12.2, JP13.2, JP14.2, JP32.2
BAT+: IC1.1 (VI), X1.2
D1: U1.D1 (IO1)
D2: R14.1, U1.D2 (IO2)
D3: R23.1, U1.D3 (IO3)
D4: R15.1, U1.D4 (IO4)
D5: R19.1, U1.D5 (IO5)
D12: R2.1, U1.D12 (IO12)
D13: R1.1, U1.D13 (IO13)
D14: R3.1, U1.D14 (IO14)
D15: R13.1, U1.D15 (IO15)
D16: R16.1, U1.D16 (IO16)
D17: R17.1, U1.D17 (IO17)
D18: R20.1, U1.D18 (IO18)
D19: R21.1, U1.D19 (IO19)
D21: R22.1, U1.D21 (IO21)
D22: R26.1, U1.D22 (IO22)
D23: R24.1, U1.D23 (IO23)
D25: R11.2, U1.D25 (IO25)
D26: R12.2, U1.D26 (IO26)
D27: R4.1, U1.D27 (IO27)
D32: R6.1, U1.D32 (IO32)
D33: R5.1, U1.D33 (IO33)
D34: R8.1, U1.D34 (IO34)
D35: R7.1, U1.D35 (IO35)
D36: Q13.3 (C), R10.1, R29.2, U1.D36 (VP-OI36)
D39: R9.1, U1.D39 (VN-IO39)
GND: C1.-, IC1.2 (GND), IC2.1 (GND), IC2.4 (IN_GND), JP1.1, JP2.1, JP3.1, JP4.1, JP5.1, JP6.1, JP7.1, JP8.1, JP9.1, JP10.1, JP11.1, JP12.1, JP13.1, JP14.1, JP32.1, Q1.1 (E), Q2.1 (E), Q3.1 (E), Q4.1 (E), Q5.1 (E), Q6.1 (E), Q7.1 (E), Q8.1 (E), Q9.1 (E), Q10.1 (E), Q11.S, Q12.1 (E), Q13.1 (E), R18.A, R25.1, U1.GND@1 (GND), U1.GND@2 (GND), X1.1
INDICATOR_L: JP16.2, JP20.4, Q2.3 (C), R27.1
INDICATOR_R: JP17.2, JP20.2, Q3.3 (C), R30.1
unnamed: IC2.3 (IN_R), IC2.5 (IN_L), R18.S
unnamed: R11.1, R12.1, R18.E
unnamed: JP1.3, JP2.3, R1.2
unnamed: Q11.G, R24.2, R25.2
unnamed: JP3.3, JP4.3, R2.2
unnamed: JP5.3, JP6.3, R3.2
unnamed: JP7.3, JP8.3, R4.2
unnamed: JP9.3, R5.2
unnamed: D1.C, U1.VIN
unnamed: JP10.3, R6.2
unnamed: JP11.3, R7.2
unnamed: JP12.3, R8.2
unnamed: JP13.3, R9.2
unnamed: JP14.3, R10.2
unnamed: D2.A, JP29.2, Q11.D
unnamed: Q10.2 (B), R23.2
unnamed: Q4.2 (B), R16.2
unnamed: JP27.2, JP28.2, Q10.3 (C)
unnamed: JP18.2, JP19.2, Q4.3 (C)
unnamed: Q1.2 (B), R13.2
unnamed: JP30.2, R27.2
unnamed: Q2.2 (B), R14.2
unnamed: JP30.4, R30.2
unnamed: Q3.2 (B), R15.2
unnamed: JP30.6, R28.2
unnamed: Q5.2 (B), R17.2
unnamed: Q6.2 (B), R19.2
unnamed: JP21.2, JP22.2, Q6.3 (C)
unnamed: Q7.2 (B), R20.2
unnamed: JP23.2, JP24.2, Q7.3 (C)
unnamed: Q8.2 (B), R21.2
unnamed: JP25.2, Q8.3 (C)
unnamed: Q9.2 (B), R22.2
unnamed: JP26.2, Q9.3 (C)
unnamed: Q12.2 (B), R26.2
unnamed: JP31.2, Q12.3 (C)
unnamed: Q13.2 (B), R31.2
REVERSING: JP20.1, Q5.3 (C)
SBUS: JP32.3, R31.1
TAILLIGHTS: JP20.3, Q1.3 (C), R28.1

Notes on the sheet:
Speaker 1
Speaker 2
13 CH1 Steering
12 CH2 Shifting
14 CH3 Throttle
27 CH4 Pot
33 ESC Output
32 Upper Brake Lights
PPM Input
39 (Serial Tx Dummy)
Serial Rx
DAC 1 & 2 Mixer Resistors
Audio amplifier
Volume Potentiometer
5V power supply for amplifier
Battery input 7.0 - 12.6V
Board for 30 pin ESP32 V1.1
Shaker motor
Headlights
Foglights
Taillights
Indicator L
Indicator R
Roof lights
Side lights
Reversing lights
Connector for TAMIYA trailer light set 56502
Rear lights
ESP32 RC Sound & Light Controller https://github.com/TheDIYGuy999/Rc_Engine_Sound_ESP32
LED driver transistors. Never connect LED directly, always use a matching series resistor!
Beacon 2
Beacon 1
Cabin lights
SBUS signal inverter
For amplifier support only
Pay attention to correct polarity!
Max. input signal voltage = 3.3V!

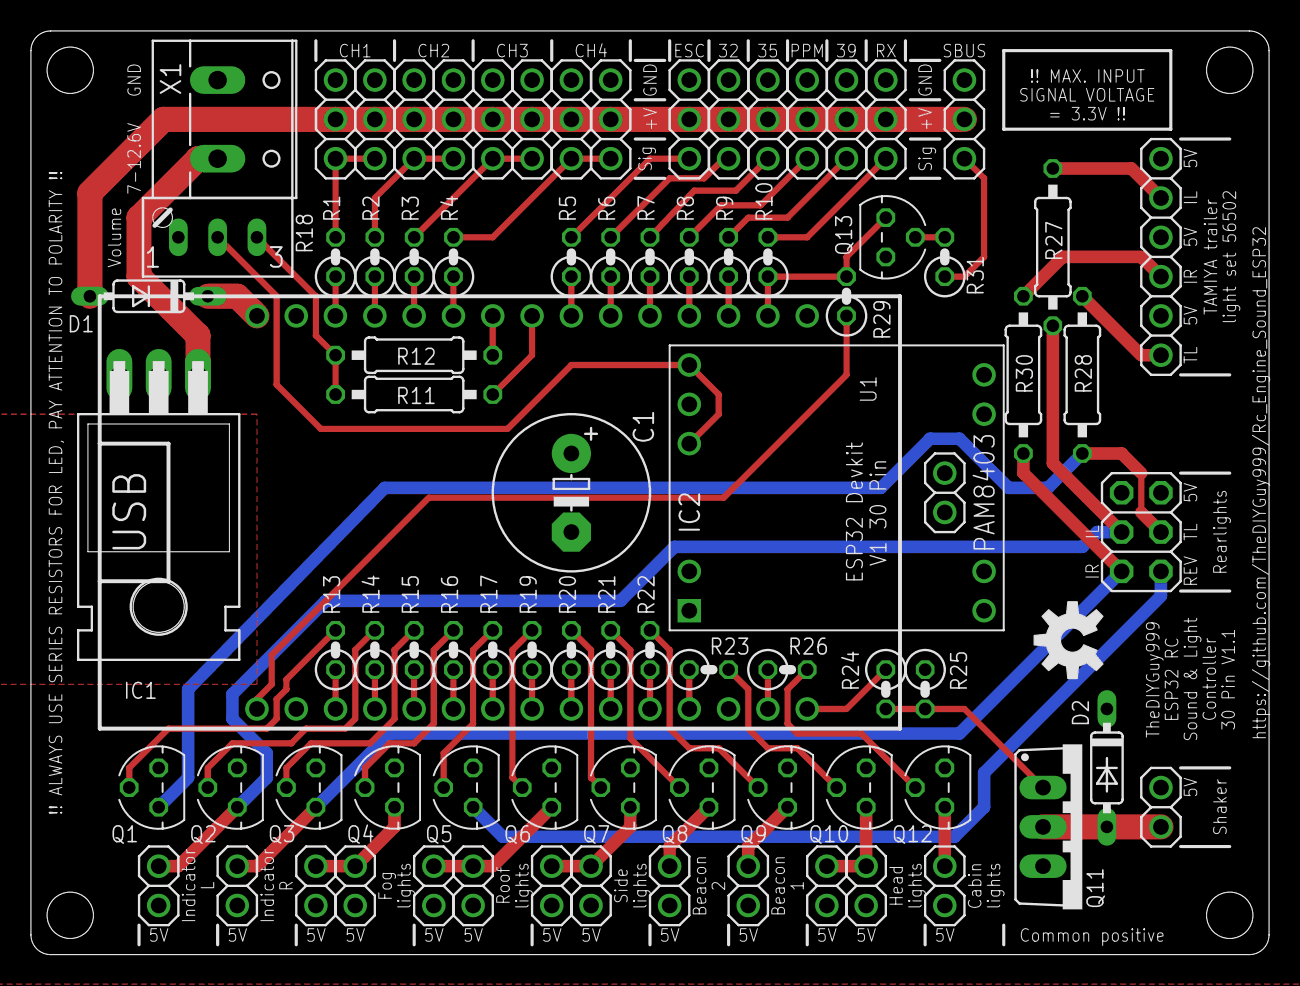
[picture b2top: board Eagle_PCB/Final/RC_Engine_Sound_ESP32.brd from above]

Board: 2 copper layers, 80.0 x 59.7 mm, 84 parts (0 on the bottom side), 71 nets.

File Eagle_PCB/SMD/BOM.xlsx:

Comment | Designator | Footprint | LCSC Part #（optional）
 | JP16, JP17, JP18, JP19, JP21, JP22, JP23, JP24, JP25, JP26, JP27, JP28, JP29, J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 | 1X02
 | JP1, JP2, JP3, JP4, JP5, JP6, JP7, JP8, JP9, JP10, JP11, JP12, JP14 | 1X03
 | JP30 | 1X07
 | JP20 | 2X03
 | X1 | W237-132
1000uF | C1 | E5-10,5
100nF | C2, C3 | C0805
10k | R11, R12 | R0805
200R | R9, R27, R30 | R0805
20k | R18 | S64W
330R | R1, R2, R3, R4, R5, R6, R7, R8, R10 | R0805
47R | R28 | R0805
7805DT | IC1 | TO252 |  | CJ7805
ESP32DEVKITV1 | U1 | ESP32-DEVKITV1
OSHW-LOGOM | LOGO1 | OSHW-LOGO-M
PAM8403_NO_SPEAKERS | IC4 | PAM8403_NO_SPEAKERS
SS14 | D1, D2 | SMA-DIODE | C2480
ULN2003AD | IC2, IC3 | SO16

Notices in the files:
parts and their libraries:
SparkFun-Aesthetics: Licensing: Creative Commons ShareAlike 4.0 International - https://creativecommons.org/licenses/by-sa/4.0
